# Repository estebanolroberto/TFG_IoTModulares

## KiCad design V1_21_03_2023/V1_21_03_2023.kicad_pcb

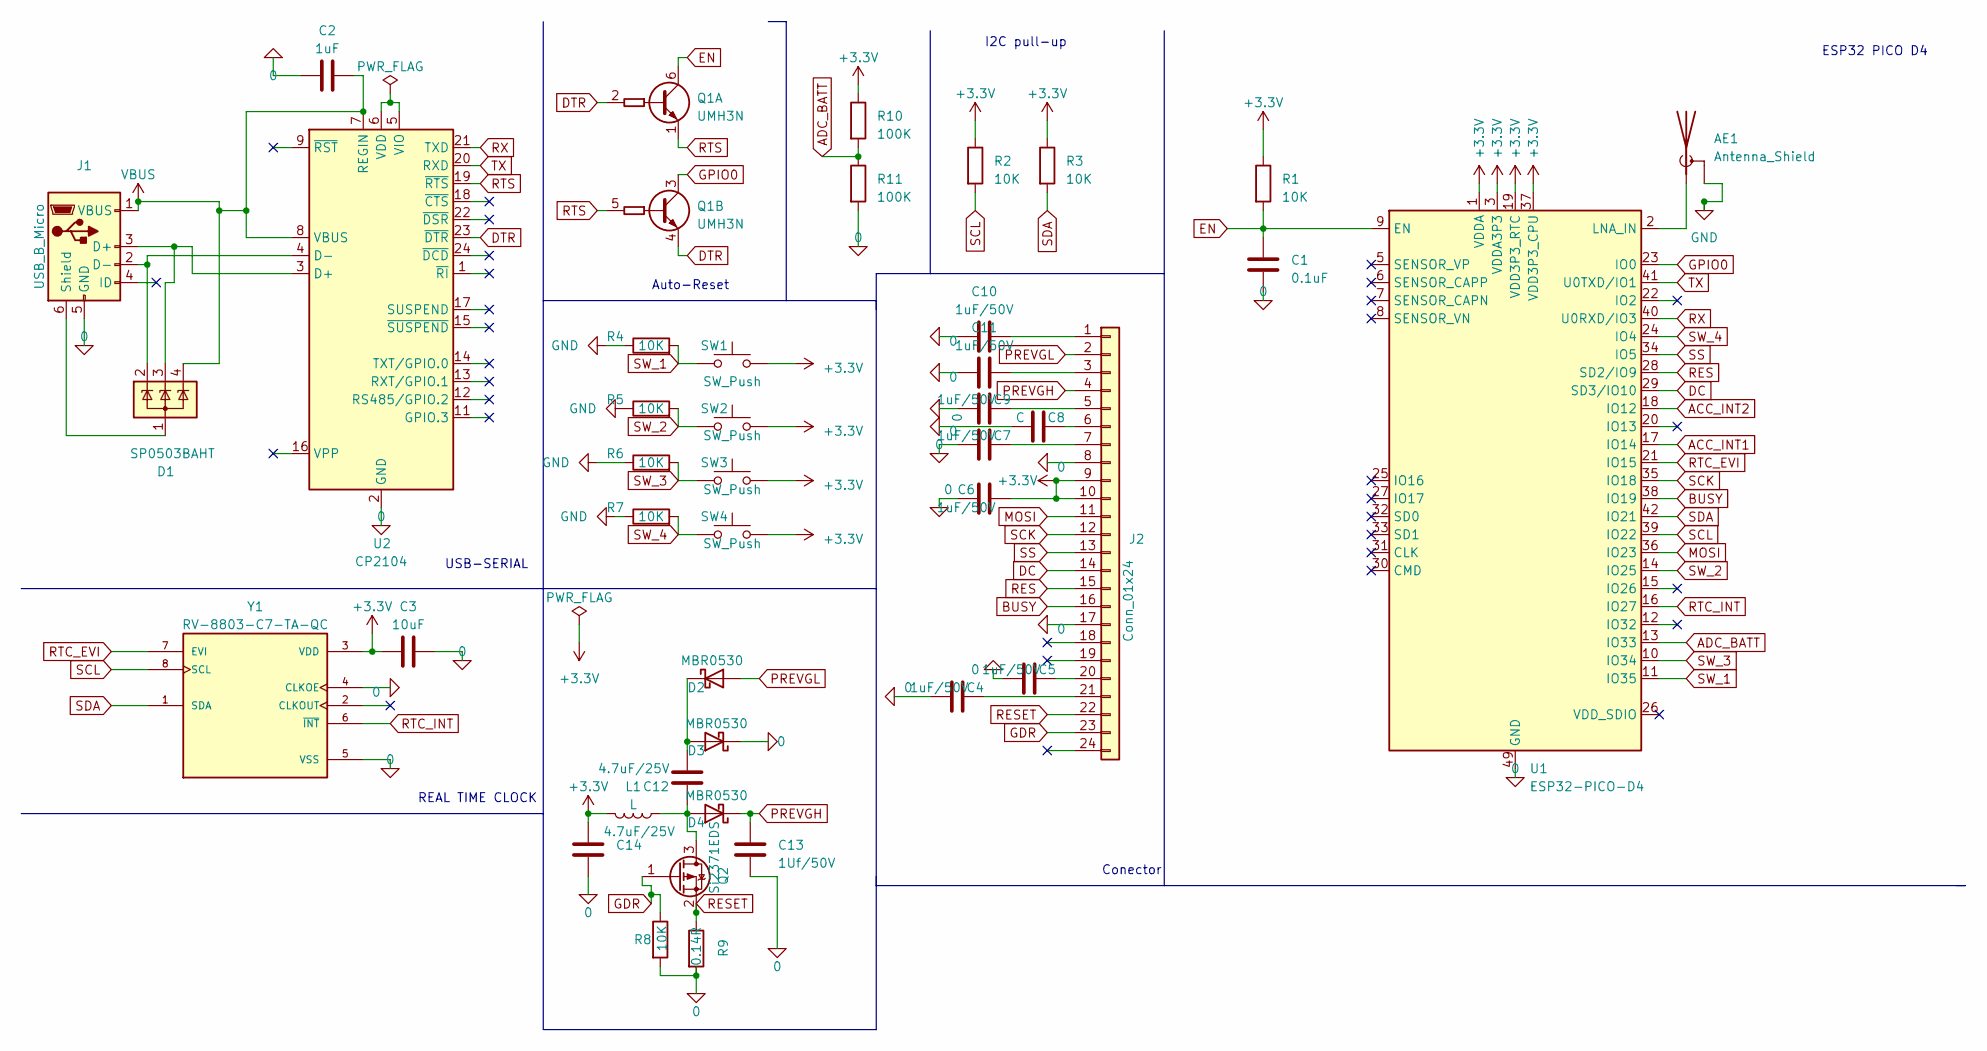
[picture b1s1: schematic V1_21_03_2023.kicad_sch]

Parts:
AE1: Antenna_Shield; Texas_SWRA117D_2.4GHz_Right
C1: 0.1uF; C_0201_0603Metric
C2: 1uF; C_0201_0603Metric
C3: 10uF; C_0201_0603Metric
C4, C5, C6, C7, C9, C10, C11: 1uF/50V; C_0201_0603Metric
C8: C; C_0201_0603Metric
C12, C14: 4.7uF/25V; C_0201_0603Metric
C13: 1Uf/50V; C_0201_0603Metric
D1: SP0503BAHT; SOT-143
D2, D3, D4: MBR0530; D_SOD-123
J1: USB_B_Micro; USB_Micro-AB_Molex_47590-0001
J2: Conn_01x24; Molex_SL_171971-0024_1x24_P2.54mm_Vertical
L1: L; L_6.3x6.3_H3
Q1: UMH3N; SOT-363_SC-70-6
Q2: Si2371EDS; SOT-23
R1, R2, R3, R4, R5, R6, R7, R8: 10K; R_0201_0603Metric
R9: 0.14R; R_0201_0603Metric
R10, R11: 100K; R_0402_1005Metric
SW1, SW2, SW3, SW4: SW_Push; SW_SPST_CK_RS282G05A3
U1: ESP32-PICO-D4; QFN-48-1EP_7x7mm_P0.5mm_EP5.3x5.3mm
U2: CP2104; QFN-24-1EP_4x4mm_P0.5mm_EP2.6x2.6mm
Y1: RV-8803-C7-TA-QC; MICROCRYSTAL_RV-8803-C7-TA-QC; PARTREV 2.0

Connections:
0: C1.2, C2.1, C3.2, C4.1, C5.1, C6.1, C7.1, C8.1, C9.1, C10.1, C11.1, C13.2, C14.2, D3.1 (K), J1.5 (GND), J2.8, J2.17, R8.2, R9.2, R11.2, U1.49 (GND), U2.2 (GND), U2.25 (GND), Y1.4 (CLKOE), Y1.5 (VSS)
+3.3V: C3.1, C6.2, C14.1, J2.9, J2.10, L1.2, R1.1, R2.1, R3.1, R10.1, SW1.2, SW2.2, SW3.2, SW4.2, U1.1 (VDDA), U1.3 (VDDA3P3), U1.4 (VDDA3P3), U1.19 (VDD3P3_RTC), U1.37 (VDD3P3_CPU), U1.43 (VDDA), U1.46 (VDDA), Y1.3 (VDD)
ACC_INT1: U1.17 (IO14)
ACC_INT2: U1.18 (IO12)
ADC_BATT: R10.2, R11.1, U1.13 (IO33)
BUSY: J2.16, U1.38 (IO19)
DC: J2.14, U1.29 (SD3/IO10)
DTR: Q1.2 (B1), Q1.4 (E2), U2.23 (~DTR)
EN: C1.1, Q1.6 (C1), R1.2, U1.9 (EN)
GDR: J2.23, Q2.1 (G), R8.1
GND: AE1.2 (Shield), R4.1, R5.1, R6.1, R7.1
GPIO0: Q1.3 (C2), U1.23 (IO0)
MOSI: J2.11, U1.36 (IO23)
unnamed: AE1.1 (A), U1.2 (LNA_IN)
unnamed: D1.1 (A), J1.6 (Shield)
unnamed: C12.1, D2.1 (K), D3.2 (A)
unnamed: C12.2, D4.2 (A), L1.1, Q2.3 (D)
unnamed: D1.3 (K), J1.3 (D+), U2.3 (D+)
unnamed: D1.2 (K), J1.2 (D-), U2.4 (D-)
unnamed: C10.2, J2.1
unnamed: C11.2, J2.3
unnamed: C9.2, J2.5
unnamed: C8.2, J2.6
unnamed: C7.2, J2.7
unnamed: C5.2, J2.20
unnamed: C4.2, J2.21
unnamed: U2.5 (VIO), U2.6 (VDD)
PREVGH: C13.1, D4.1 (K), J2.4
PREVGL: D2.2 (A), J2.2
RES: J2.15, U1.28 (SD2/IO9)
RESET: J2.22, Q2.2 (S), R9.1
RTC_EVI: U1.21 (IO15), Y1.7 (EVI)
RTC_INT: U1.16 (IO27), Y1.6 (~INT)
RTS: Q1.1 (E1), Q1.5 (B2), U2.19 (~RTS)
RX: U1.40 (U0RXD/IO3), U2.21 (TXD)
SCK: J2.12, U1.35 (IO18)
SCL: R2.2, U1.39 (IO22), Y1.8 (SCL)
SDA: R3.2, U1.42 (IO21), Y1.1 (SDA)
SS: J2.13, U1.34 (IO5)
SW_1: R4.2, SW1.1, U1.11 (IO35)
SW_2: R5.2, SW2.1, U1.14 (IO25)
SW_3: R6.2, SW3.1, U1.10 (IO34)
SW_4: R7.2, SW4.1, U1.24 (IO4)
TX: U1.41 (U0TXD/IO1), U2.20 (RXD)
VBUS: C2.2, D1.4 (K), J1.1 (VBUS), U2.7 (REGIN), U2.8 (VBUS)

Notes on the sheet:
I2C pull-up
Conector
REAL TIME CLOCK
USB-SERIAL
ESP32 PICO D4
Auto-Reset

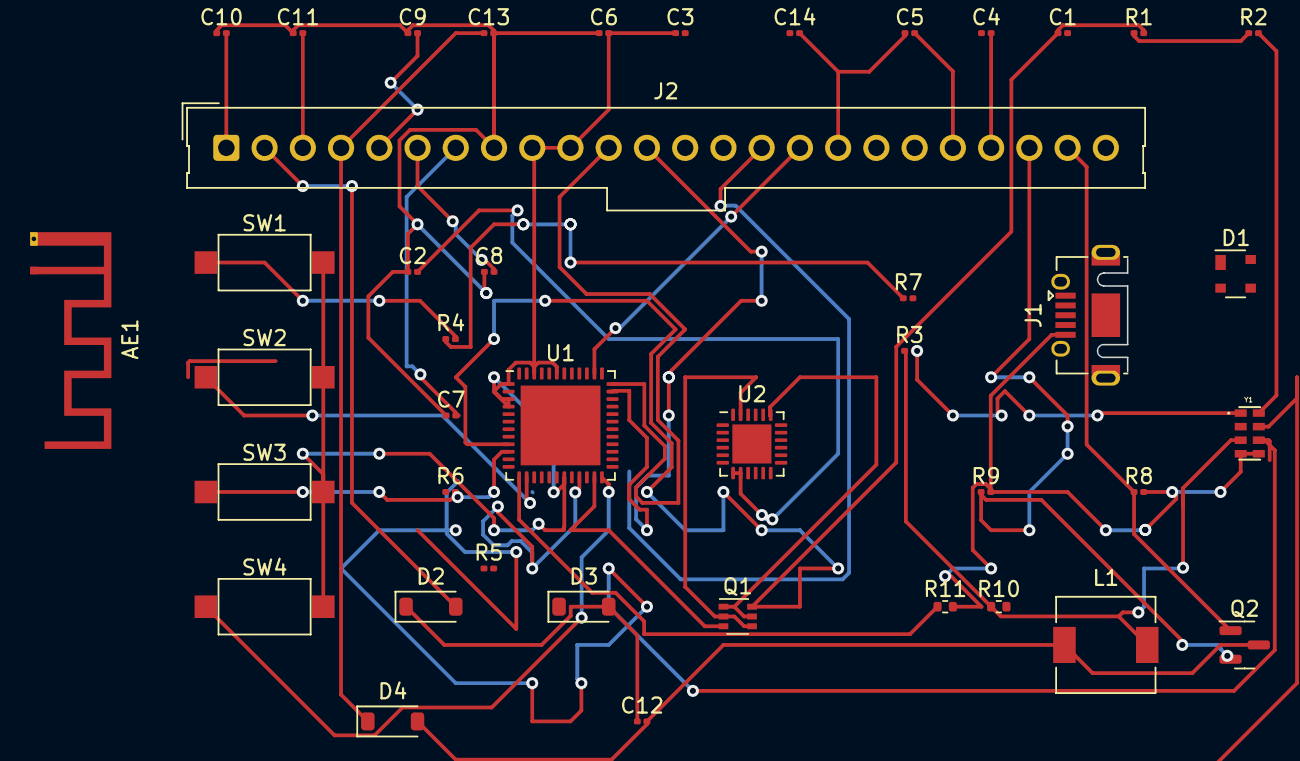
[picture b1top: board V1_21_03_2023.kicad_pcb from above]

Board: 2 copper layers, 42 parts (0 on the bottom side), 43 nets.

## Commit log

2023-03-21 Test con PICP-D4
2023-03-23 Se añaden más elementos al schematic
2023-03-26 Terminado Schematic
2023-04-03 Pruebas conexion de cables
